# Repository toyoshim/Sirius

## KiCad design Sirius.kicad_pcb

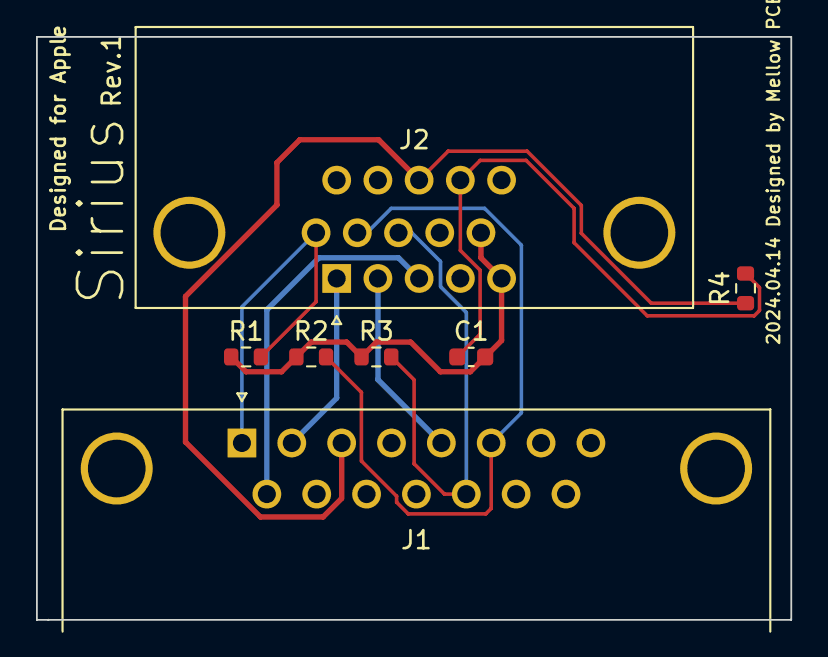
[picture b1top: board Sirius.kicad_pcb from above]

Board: 2 copper layers, 41.9 x 32.4 mm, 7 parts (0 on the bottom side), 9 nets.

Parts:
C1: 10u; C_0603_1608Metric
J1: DB15_Male; DSUB-15_Male_Horizontal_P2.77x2.84mm_EdgePinOffset7.70mm_Ho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
J2: DB15_Female_HighDensity; DSUB-15-HD_Female_A_HDF15A_KG_TAXB
R1, R2, R3: 1k; R_0603_1608Metric
R4: 160; R_0603_1608Metric

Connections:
/B: J1.9, J2.3
/BGND: J1.13, J2.8, R3.2
/CSYNC: J1.3, J2.13, R4.1
/G: J1.5, J2.2
/GGND: J1.6, J2.7, R2.2
/R: J1.2, J2.1
/RGND: J1.1, J2.6, R1.2
/VSYNC: C1.1, J2.14, R4.2
GND: C1.2, J2.5, J2.10, R1.1, R2.1, R3.1

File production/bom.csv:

Designator,Footprint,Quantity,Value,LCSC Part #
C1,0603,1,10u,
J1,DSUB-15_Male_Horizontal_P2.77x2.84mm_EdgePinOffset7.70mm_Housed_MountingHolesOffset9.12mm,1,DB15_Male,
J2,DSUB-15-HD_Female_A_HDF15A_KG_TAXB,1,DB15_Female_HighDensity,
"R1, R2, R3",0603,3,1k,
R4,0603,1,160,
